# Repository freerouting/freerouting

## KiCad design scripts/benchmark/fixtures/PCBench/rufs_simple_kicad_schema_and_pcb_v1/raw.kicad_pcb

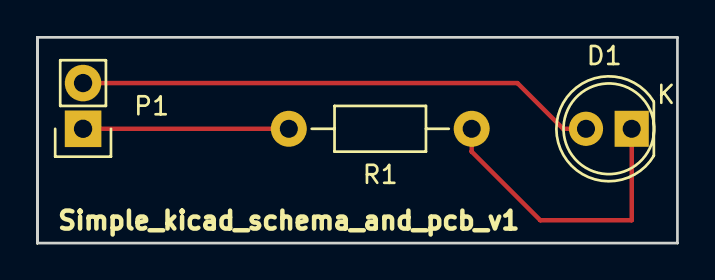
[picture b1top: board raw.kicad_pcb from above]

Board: 2 copper layers, 35.6 x 11.4 mm, 3 parts (0 on the bottom side), 3 nets.

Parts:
D1: LED; LED-5MM
P1: Power; Pin_Header_Straight_1x02
R1: 330; Resistor_Horizontal_RM10mm

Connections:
GND: D1.2, P1.2
unnamed: D1.1, R1.1
VCC: P1.1, R1.2

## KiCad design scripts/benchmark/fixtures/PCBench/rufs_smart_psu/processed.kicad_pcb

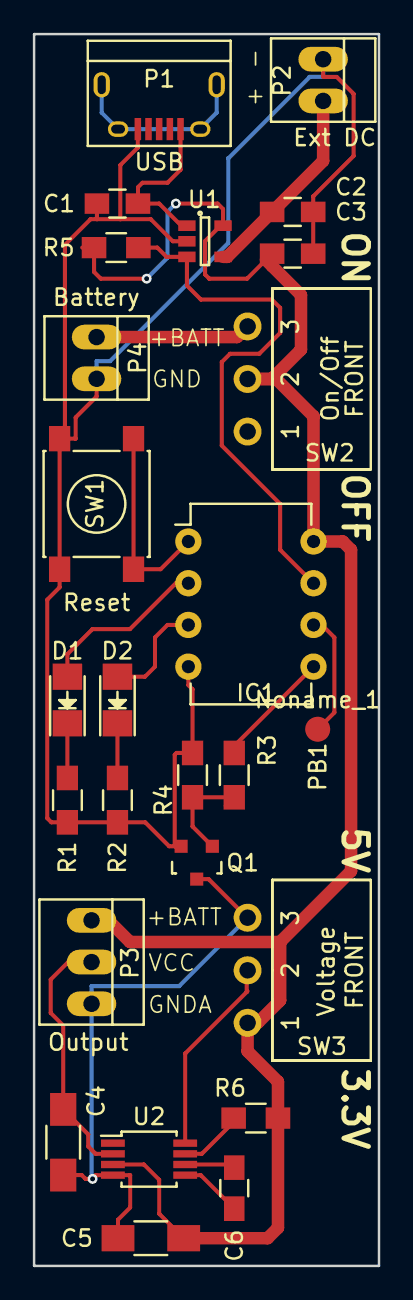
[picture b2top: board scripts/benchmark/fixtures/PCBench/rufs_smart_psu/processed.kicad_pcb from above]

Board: 2 copper layers, 21.0 x 75.0 mm, 26 parts (0 on the bottom side), 20 nets.

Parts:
C1, C2, C3, C6: C_0805_HandSoldering
C4, C5: C_1206_HandSoldering
D1, D2: LED_1206
IC1: DIP-8_W7.62mm
Noname_1: PB1; Measurement_Point_Round-SMD-Pad_Small
P1: USB; USB_Micro-B
P2: Ext DC; PINHEAD1-2
P3: Output; PINHEAD1-3
P4: Battery; PINHEAD1-2
Q1: SOT-23
R1, R2, R3, R4, R5, R6: R_0805_HandSoldering
SW1: Reset; SW_SPST_PTS645
SW2: On/Off; spdt_slide_switch_angled
SW3: Voltage; spdt_slide_switch_angled
U1: SOT-23-5
U2: MSOP-8_3x3mm_Pitch0.65mm

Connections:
+BATT: C3.1, C5.1, IC1.8, P3.1, R5.2, R6.2, SW2.2, SW3.1, U1.5, U2.3
GND: C1.1, C2.2, C3.2, IC1.4, P1.5, P2.1, P4.2, Q1.3, R1.2, R2.2, R4.2, SW1.1, U1.2
GNDA: C4.2, C5.2, P3.3, Q1.1, SW3.3, U2.4
unnamed: C1.2, P1.1, U1.1
unnamed: C2.1, P2.2, U1.4
unnamed: C6.1, U2.6
unnamed: C6.2, U2.5
unnamed: D1.1, R1.1
unnamed: D1.2, IC1.2
unnamed: D2.1, R2.1
unnamed: D2.2, IC1.3
unnamed: IC1.1, SW1.2
unnamed: IC1.5, R3.2
unnamed: IC1.6, Noname_1.1
unnamed: IC1.7, R5.1, U1.3
unnamed: P4.1, SW2.3
unnamed: Q1.2, R3.1, R4.1
unnamed: R6.1, U2.7
unnamed: SW3.2, U2.8
VCC: C4.1, P3.2, U2.2

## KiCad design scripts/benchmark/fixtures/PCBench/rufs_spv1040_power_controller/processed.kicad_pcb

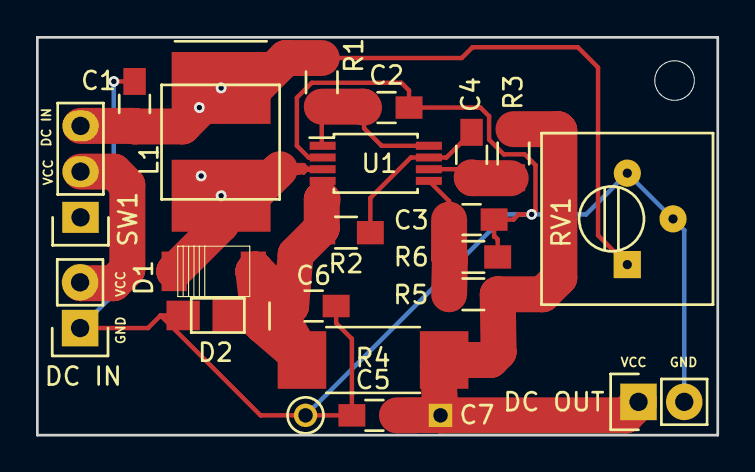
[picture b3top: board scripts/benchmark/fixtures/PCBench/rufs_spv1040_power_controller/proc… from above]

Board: 2 copper layers, 37.8 x 22.1 mm, 21 parts (0 on the bottom side), 10 nets.

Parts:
C1, C2, C5, C6: 10uF; C_0805_HandSoldering
C3: 1nF; C_0805_HandSoldering
C4: 1uF; C_0805_HandSoldering
C7: 4700uF; C_Radial_D16_L25_P7.5
D1: D_Schottky; SOD-128
D2: TVS; STmite_flat_DO216-AA
DC IN: DC IN; Pin_Header_Straight_1x02
DC OUT: DC OUT; Pin_Header_Straight_1x02
L1: 10uH; XAL6060
R1, R2, R3: 1K; R_0805_HandSoldering
R4: 10m; R_2512_HandSoldering
R5: 1M; R_0805_HandSoldering
R6: 330K; R_0805_HandSoldering
RV1: POT; Potentiometer_Trimmer-Suntan-TSR-3386P
SW1: SWITCH_INV; Pin_Header_Straight_1x03
U1: SPV1040; TSSOP-8_4.4x3mm_Pitch0.65mm

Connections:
GND: C1.2, C2.2, C3.2, C5.2, C6.2, C7.2, D2.1, DC IN.1, DC OUT.2, R6.2, RV1.2, RV1.3, U1.2
unnamed: C1.1, L1.2, R1.1, RV1.1, SW1.3
unnamed: C2.1, R1.2, U1.1, U1.8
unnamed: C3.1, R5.2, R6.1, U1.5
unnamed: C4.1, R2.2, U1.7
unnamed: C4.2, R3.2, U1.6
unnamed: C5.1, C7.1, DC OUT.1, R3.1, R4.1, R5.1
unnamed: C6.1, D1.1, D2.2, R2.1, R4.2, U1.4
unnamed: D1.2, L1.1, U1.3
VCC: DC IN.2, SW1.2
